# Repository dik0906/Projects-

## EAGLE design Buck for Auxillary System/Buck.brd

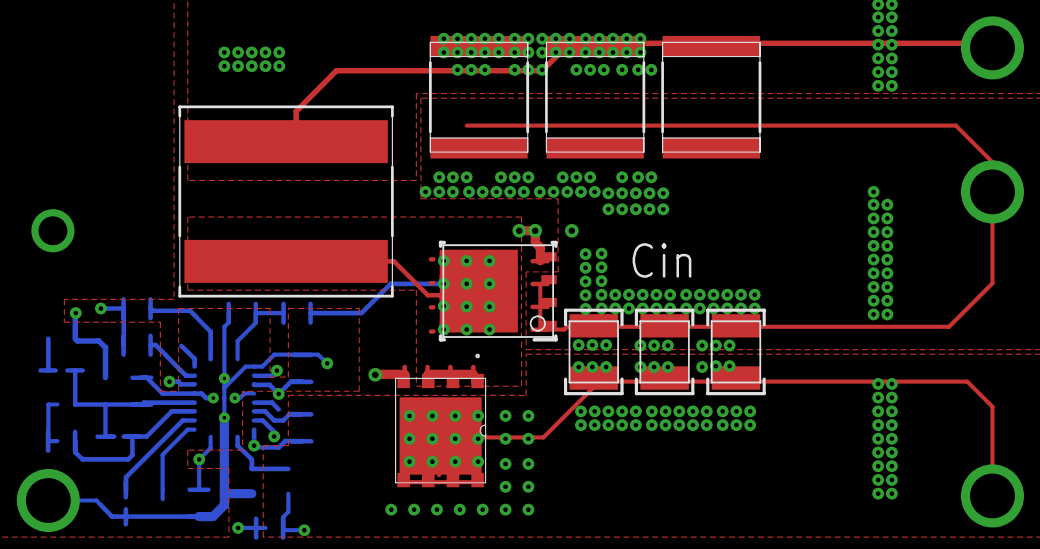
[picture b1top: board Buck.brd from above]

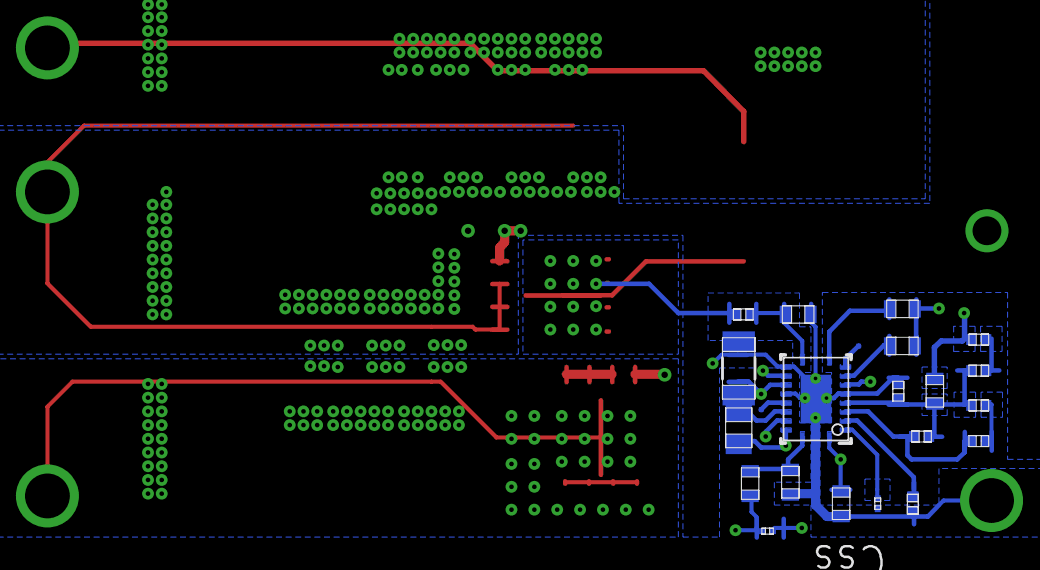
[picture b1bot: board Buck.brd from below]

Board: 4 copper layers, 37 parts (23 on the bottom side), 22 nets.

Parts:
AGND: TP-1502
Cboot: 0805
Ccomp1, Ccomp2, Ccomp3: 0402
Cilim: 0603
Cin_1, Cin_2, Cin_3: 1210
Cout_1, Cout_2, Cout_3: 2220_250
Css_1, Css_2: 0402
Cvcc: 1206
Cvin: 0603
L1: XAL1010
M1: TRANS_NexFET_Q5A
M2: TRANS_NexFET_Q5B
NC1, NC2: SMD_PAD1
PGND: TP-1502
Rcomp1, Rcomp2: 0402
Rfbb: 0402
Rfbt: 0603
Rilim: 0402
Rpgood: 0603
Rt: 0201
Ruv1: 0201
Ruv2: 0603
Rvcc: 0603
Rvin: 0603
SYNCOUT: TP-5012
U1: RGY0020B
VIN: TP-1502
VOUT: TP-1502

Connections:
0: AGND.1, Cilim.1, Cin_1.2, Cin_2.2, Cin_3.2, Cout_1.2, Cout_2.2, Cout_3.2, Css_1.2, Css_2.2, Cvcc.2, Cvin.2, M2.1, M2.2, M2.3, PGND.1, Rfbb.1, Rt.2, Ruv2.2, U1.6, U1.12, U1.15, U1.21
1: Cvcc.1, Rpgood.1, Rvcc.2, U1.14
2: Cout_1.1, Cout_2.1, Cout_3.1, L1.1, Rcomp2.1, Rfbt.1, VOUT.1
3: Cin_1.1, Cin_2.1, Cin_3.1, M1.5, M1.6, M1.7, M1.8, M1.9, Ruv1.1, Rvin.1, VIN.1
4: Ruv1.2, Ruv2.1, U1.1
7: Css_1.1, Css_2.1, U1.3
8: Cvin.1, Rvin.2, U1.20
10: Ccomp1.1, Ccomp2.1, U1.4
11: Ccomp2.2, Ccomp3.2, Rcomp1.2, Rfbb.2, Rfbt.2, U1.5
13: Cilim.2, Rilim.2, U1.11
16: Cboot.2, L1.2, M1.1, M1.2, M1.3, M2.5, M2.6, M2.7, M2.8, M2.9, Rilim.1, U1.19
17: Ccomp1.2, Rcomp1.1
18: Ccomp3.1, Rcomp2.2
19: Rvcc.1, U1.8
21: NC2.1, U1.16
22: NC1.1, U1.9
26: Rt.1, U1.2
27: Cboot.1, U1.17
35: M1.4, U1.18
36: M2.4, U1.13
37: SYNCOUT.1, U1.7
38: Rpgood.2, U1.10
